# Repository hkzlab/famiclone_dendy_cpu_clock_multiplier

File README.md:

# Famiclone Dendy CPU clock multiplier

## DISCLAIMER

Any use of this project is **under your own responsibility**.
You will be responsible of checking the correct construction and functionality of your board.
By using this project You will agree that I cannot be held responsible if it will destroy any of your devices, damage your computer, burn down your house or whatever.

### Sponsorship

This project is sponsored by [PCBWay](https://pcbway.com)!

PCBWay specializes in manufacturing high-quality PCBs and makes them affordable to hobbyist and professionals alike.

The range of services they offer include PCB prototyping, assembly, instant quotes for your order, a verification process by a team
of experts and an easy to use, hassle-free order process.

I am extremely grateful to them, as they sponsor most of my projects, and allow me to move them forward at a pace I wouldn't be able to sustain otherwise!

## Introduction

This board is a clock multiplier for cheap Dendy Famiclone CPUs, so they can be used in NTSC systems.

You can read about Dendy Famiclones timings [here](https://forums.nesdev.org/viewtopic.php?t=20931).

Fundamentally, NTSC and "Dendy" Famicoms have the same CPU clock / PPU clock ratio of 1:3, but Dendys are meant to work with 26.601712 Mhz frequency,
instead of the standard 21.47727 Mhz frequency for NTSC Famicoms/NES.

NTSC CPUs have an internal clock divisor of 12 (21.47727 / 12 ~= 1.790Mhz), while Dendy CPUs (except for older models) have a divisor of 15 (26.601712 / 15 ~= 1.773Mhz).
The rest of the core should be the same. Hopefully.

This board should bridge the gap making a cheap Dendy CPU work on an NTSC system by multiplying the input clock of the CPU by 1.25: 21.47727 x 1.25 = 26.8465875, which,
divided by 15 yields ~1.789Mhz, almost the same as the NTSC CPU.

The board takes the input clock, divides it by 4 using a 74'74, then multiplies the result by 5 using an ICS501 PLL, 5/4 is 1.25 :)

### Rev. 1 "Between sockets" installation

Rev. 1 boards can be installed either on the underside of the motherboard, which requires then modifying the motherboard itself to interrupt the clock that goes to pin 29 of the CPU or,
optionally, between two DIP40 sockets (one on the motherboard and the one where you'll plug the CPU in).

You'll need an open-frame socket of the type shown in the picture, you'll have to cut and isolate pin 29 on the top socket (as shown in picture) and then route a wire to pick up the clock
signal from the motherboard.

If you go this route, **order boards with 1mm thickness and not 1.6!**

### Ordering the boards

You can order the board for this project at [PCBWay](https://www.pcbway.com/project/shareproject/Famiclone_Dendy_to_NTSC_CPU_adapter_Clock_Multiplier_e8107b82.html) and support me or download 
the gerbers and have them printed wherever you like!!!

## Hardware

The board was designed with [KiCad](https://kicad.org/) EDA.

### Bill of Materials

| Component              | Qty | Type / Value                                            | Notes                                                                |
| ---------------------- | --- | ------------------------------------------------------- | -------------------------------------------------------------------- |
| C1                     |  1  | 10nF/16V ceramic cap, 0805                              |                                                                      |
| C2                     |  1  | 100nF/16V ceramic cap, 0805                             |                                                                      |
| C3, C4                 |  2  | 220pF/16V ceramic cap, 0805                             | Optional, install only if you wish to decouple the clocks. Not needed in my tests. |
| R1, R2                 |  2  | 150K resistor, 0805                                     | Optional, install only if you wish to decouple the clocks. Not needed in my tests. |
| U1                     |  1  | 74HC/HCT/LS74, SOIC-14                                  | Bypassing the input clock decoupling I was able to use an 'HC on a Famicom  |
| U2                     |  1  | ICS501 PLL, SOIC-8                                      |                                                                      |

### Assembly

If you don't need to decouple the input and output clocks, you can leave out C3, C4, R1 and R2, and just close the JP1 and JP2 bridges. The rest of the components are needed.

The board is meant to be soldered on the underside of the motherboard, right under the CPU. I do recommend to put the CPU in a socket if it is not already.

Also, note that the ~26Mhz clock getting to the CPU must be intercepted and interrupted. It's quite easy to do on a Famicom, as it is sufficient to lift a leg of the decoupling capacitor C9.
The ~26Mhz clock must then be fed to the multiplier via pad J1. The empty pad that housed C9, on the Side of the Q3 transistor, is perfect for this.
In case you are installing this in a Famiclone/NES, you will have to change the location where you tap the signal from.

Note that the part of the PCB without components is the part that must face the motherboard. It is a good idea to put some tape between this PCB and the motherboard, to avoid potential shorts.

## Compatibility

I'll keep this table updated when I test new CPUs with this adapter.

| CPU Type  | Compatible | Notes                                           |
| --------- | ---------- | ----------------------------------------------- |
| TA-03NP1  | ❌         | Works, but has severe glitching and speed issues in some games  |
| UA6547P (old model, /16 divisor) | ❌ |  Works, but has severe glitching in games  |
| UA6547P (/15 divisor) | ✔️ | It Works! |
| GM6527 (/15 divisor) | ✔️ | It Works! |

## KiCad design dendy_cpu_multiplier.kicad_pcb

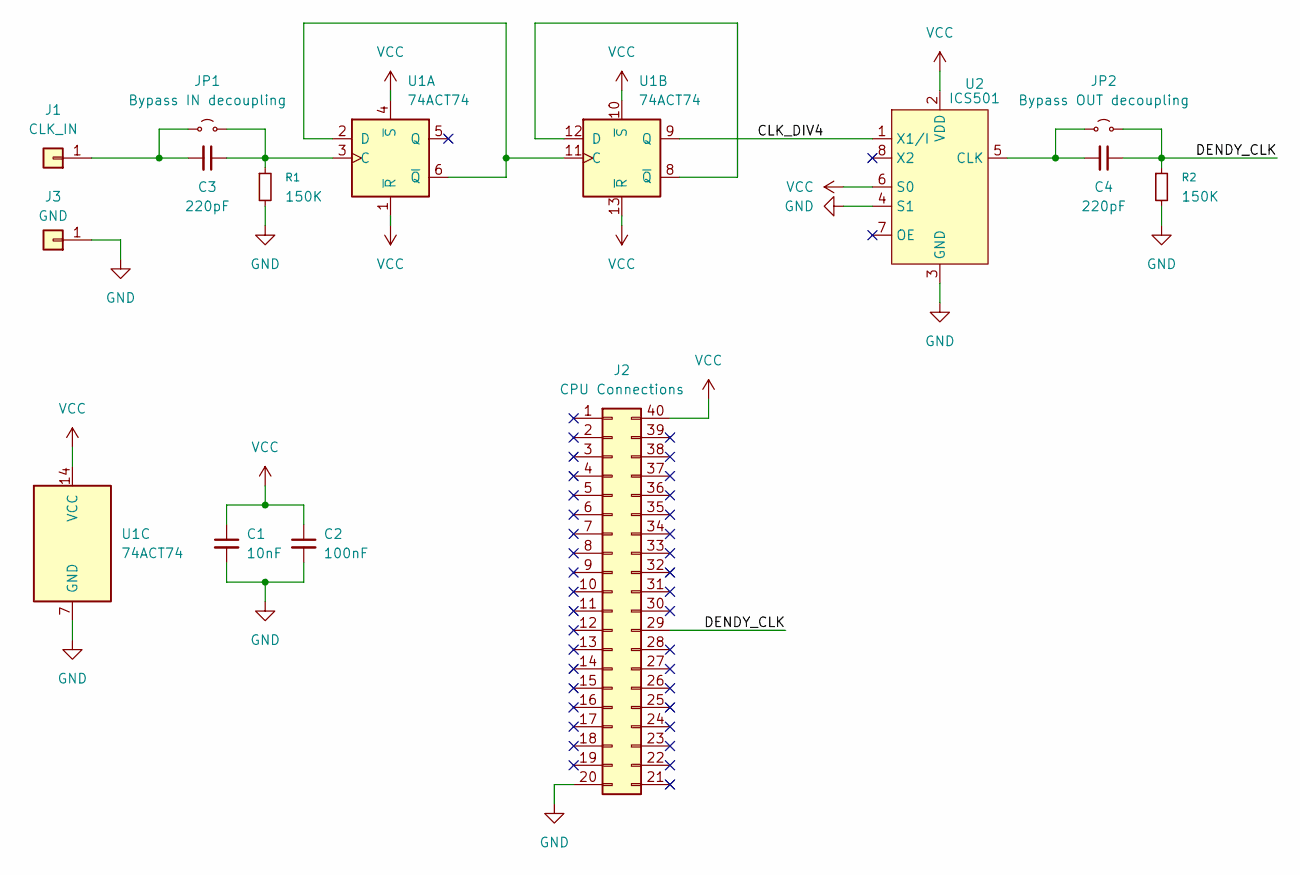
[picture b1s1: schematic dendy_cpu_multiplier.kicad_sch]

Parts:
C1: 10nF; C_0805_2012Metric_Pad1.18x1.45mm_HandSolder
C2: 100nF; C_0805_2012Metric_Pad1.18x1.45mm_HandSolder
C3, C4: 220pF; C_0805_2012Metric_Pad1.18x1.45mm_HandSolder
J1: CLK_IN; TestPoint_Pad_D1.5mm
J2: CPU Connections; DIP-40_W15.24mm
J3: GND; TestPoint_Pad_D1.5mm
JP1: Bypass IN decoupling; SolderJumper-2_P1.3mm_Open_TrianglePad1.0x1.5mm
JP2: Bypass OUT decoupling; SolderJumper-2_P1.3mm_Open_TrianglePad1.0x1.5mm
R1, R2: 150K; R_0805_2012Metric_Pad1.20x1.40mm_HandSolder
U1: 74ACT74; SOIC-14_3.9x8.7mm_P1.27mm
U2: ICS501; SOIC-8_3.9x4.9mm_P1.27mm

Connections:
/CLK_DIV4: U1.9 (Q), U2.1 (X1/I)
/DENDY_CLK: C4.1, J2.29, JP2.2 (B), R2.1
GND: C1.2, C2.2, J2.20, J3.1, R1.2, R2.2, U1.7 (GND), U2.3 (GND), U2.4 (S1)
unnamed: C3.2, J1.1, JP1.1 (A)
unnamed: C3.1, JP1.2 (B), R1.1, U1.3 (C)
unnamed: C4.2, JP2.1 (A), U2.5 (CLK)
unnamed: U1.2 (D), U1.6 (~Q), U1.11 (C)
unnamed: U1.8 (~Q), U1.12 (D)
VCC: C1.1, C2.1, J2.40, U1.1 (~R), U1.4 (~S), U1.10 (~S), U1.13 (~R), U1.14 (VCC), U2.2 (VDD), U2.6 (S0)

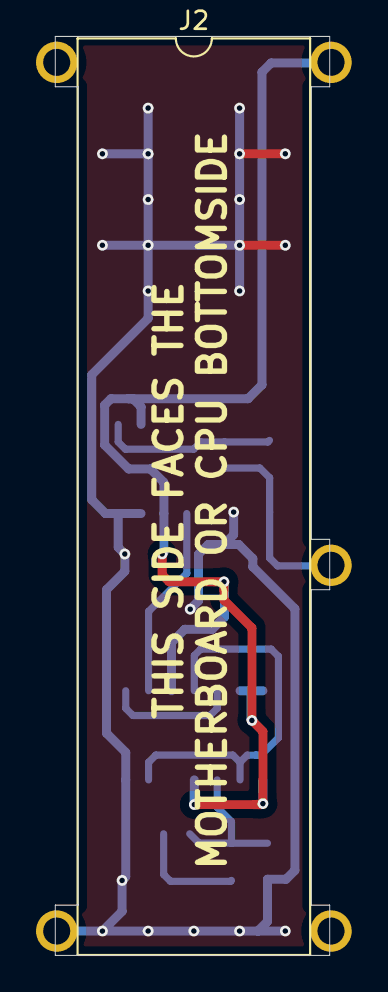
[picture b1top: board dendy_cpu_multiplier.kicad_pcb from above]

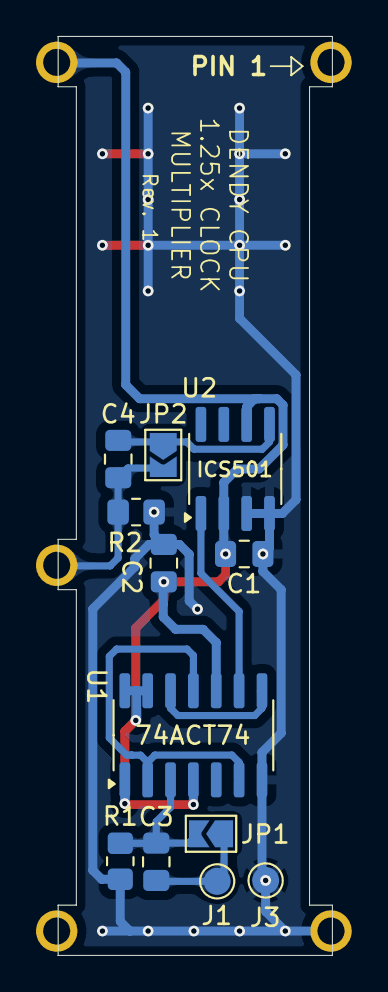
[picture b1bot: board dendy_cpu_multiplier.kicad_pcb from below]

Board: 2 copper layers, 15.2 x 51.1 mm, 13 parts (12 on the bottom side), 9 nets.

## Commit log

2025-04-02 Upload initial revision of the project
2025-04-03 Add some silkscreen tweaks
2025-04-05 Add datasheets, gerbers and schematics
2025-05-06 Add PDF schematic
2025-05-06 Mention PCBWay
2025-05-06 Add additional pics
2025-05-06 Update PCBWay link in the README
2025-05-12 Update the readme to mention GM6527
2025-12-01 Move around the components to fit into the holes of a DIP40 socket
2026-01-12 Add rev.1 PCB, untested
2026-01-31 Update README and picture. Rev.1 is tested
2026-02-02 Update the README, mention PCBWay as sponsor
